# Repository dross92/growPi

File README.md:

# **growPi**

#### Envirologger / Fan Controller for Raspberry Pi ####
This is a 'HAT' for Raspberry Pi 3 B.  The objective of this circuit board is to control and optimize an environment for growing plants.  Integrated Fan controller regulates temperature.

### Connections ###
* Headers for up to five i2c connections (Vcc = 5V)
* Three 4-wire 12v PWM fans
* Three relays (Lights, Fan, Water Pump)
* 12v plug powers entire board & Pi
* Push Button for manual pump control

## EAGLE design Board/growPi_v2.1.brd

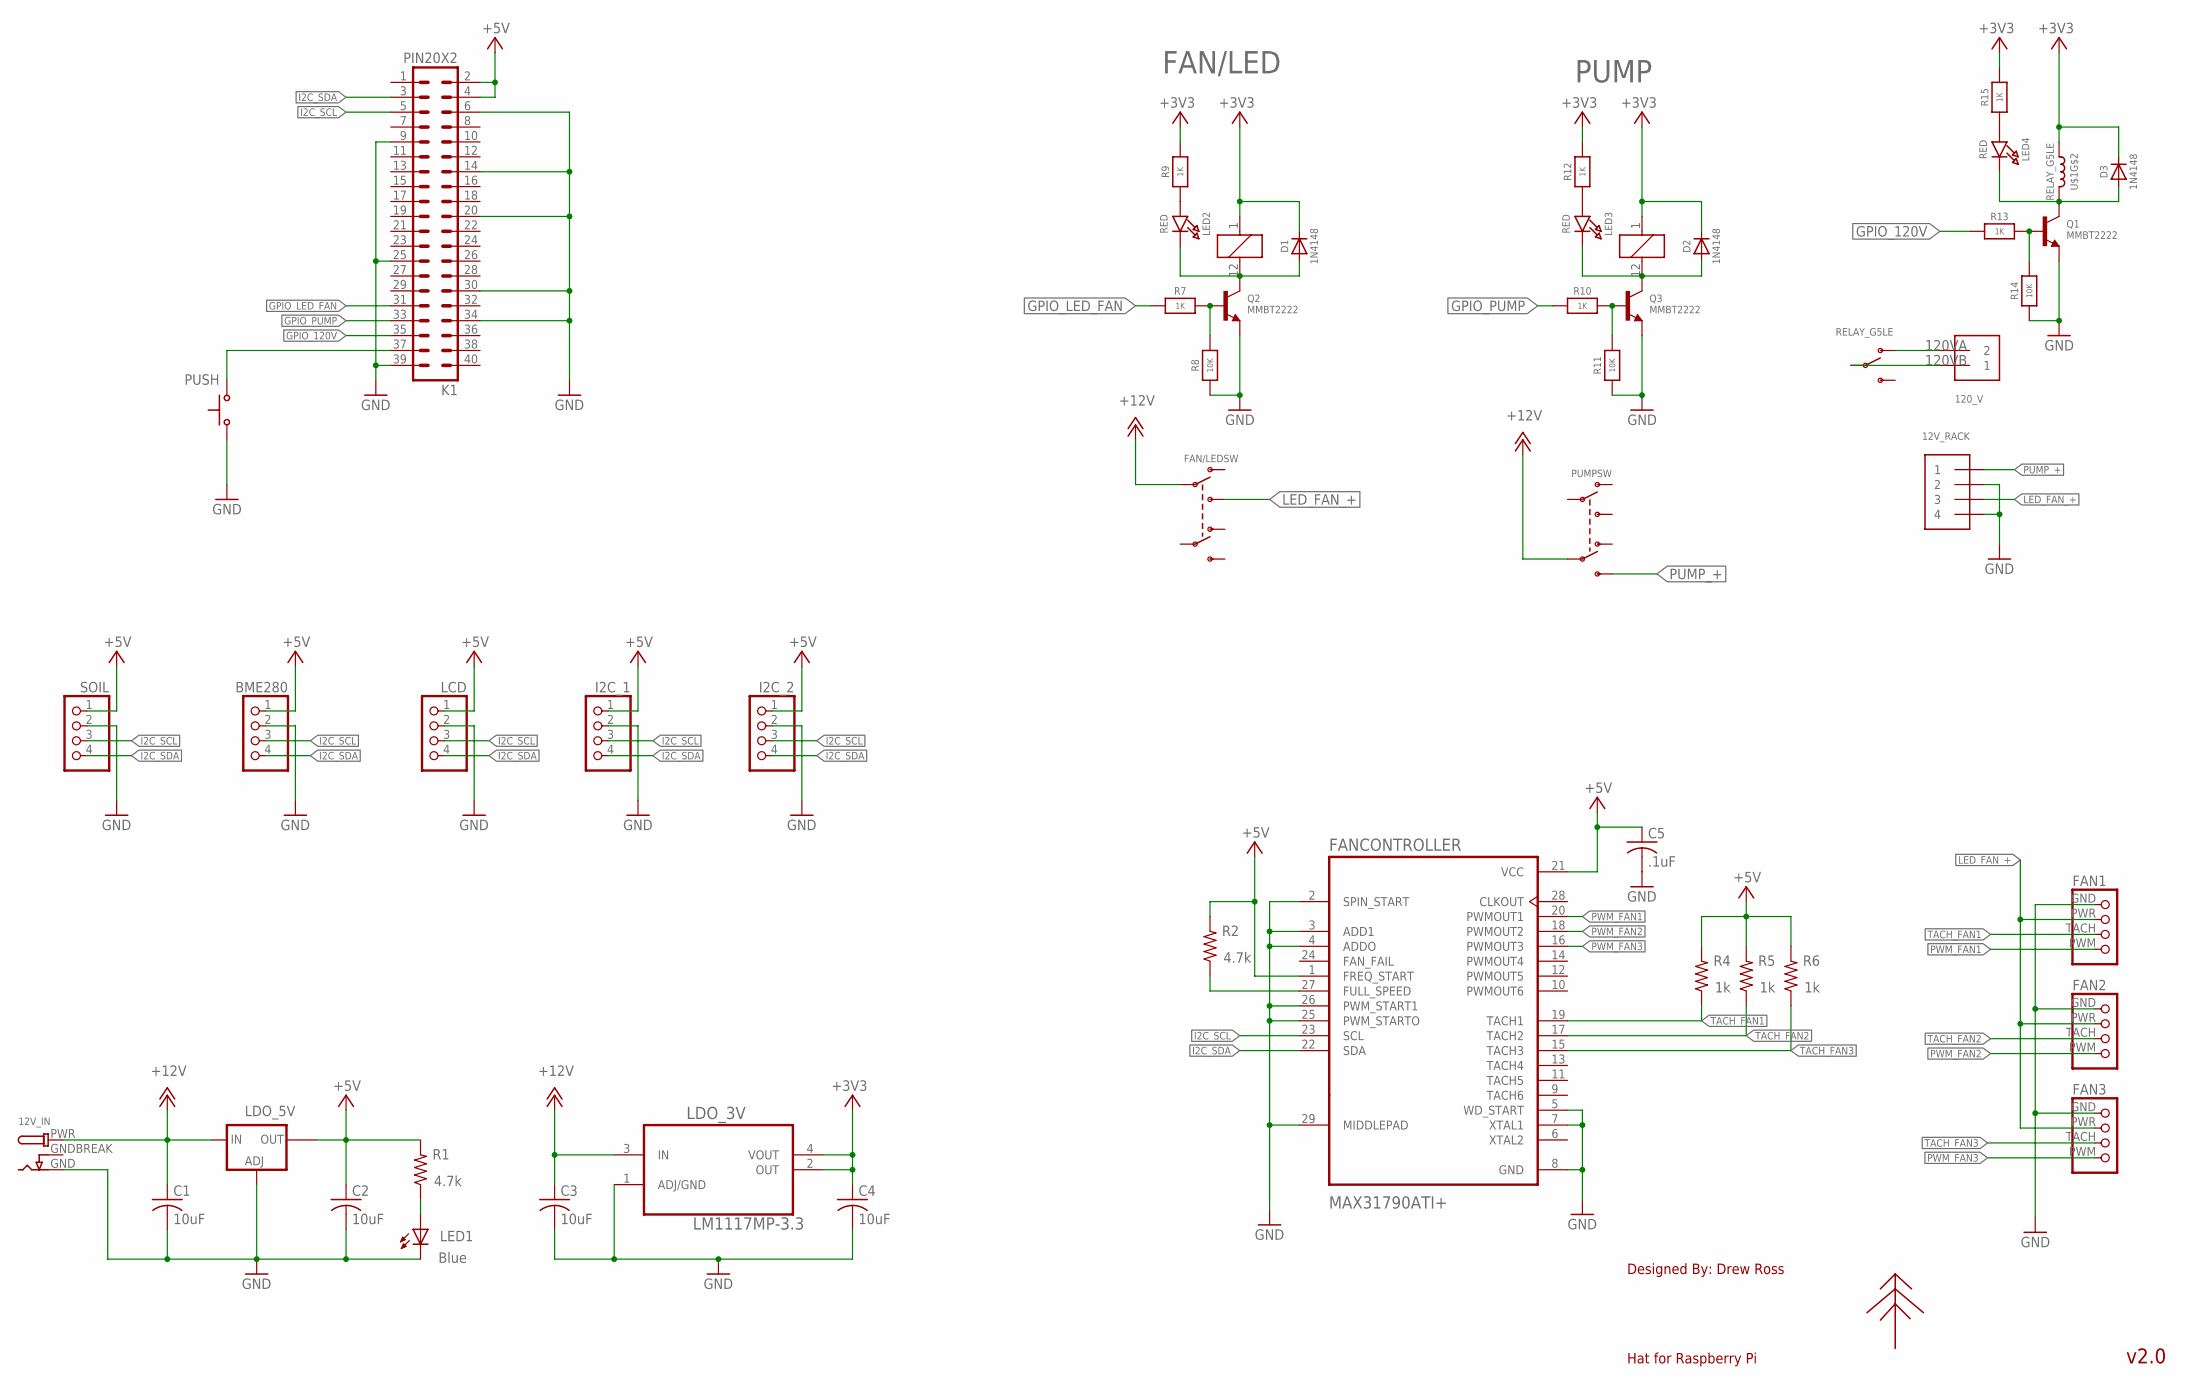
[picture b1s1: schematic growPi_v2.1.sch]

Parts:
12V_IN: DCBARRELSMT_CORRECT; DCJACK_2MM_SMT
12V_RACK: TERMBLOCK_1X4-5.0MM
120_V: TERMBLOCK_1X2-5.0MM
BME280: PINHD-1X4; 1X04
C1, C2, C3, C4: 10uF; C0603
C5: .1uF; C0603
D1, D2, D3: 1N4148; SOD-323
FAN1, FAN2, FAN3: 4PIN-MOLEX-FAN; 4PIN-FAN-HEADER
FAN/LED: RELAY_NONLATCHING-EE2NUH; RELAY_EE2_NOLATCH
FANCONTROLLER: MAX31790ATI+; QFN40P400X400X80-29N
I2C_1, I2C_2: PINHD-1X4; 1X04
K1: PIN20X2; PIN_20X2
LCD: PINHD-1X4; 1X04
LDO_3V: LM1117MP-3.3; SOT230P696X180-4N
LDO_5V: LM1084IS; TO263
LED1: Blue; CHIPLED_0603
LED2, LED3, LED4: RED; CHIPLED_0603_NOOUTLINE
PLANTLOGO: PLANTLOGO; PLANT
PUMP: RELAY_NONLATCHING-EE2NUH; RELAY_EE2_NOLATCH
PUSH: PTS645SSMTR; PTS645-SMD
Q1, Q2, Q3: MMBT2222; SOT23-R
R1, R2: 4.7k; R0603
R4, R5, R6: 1k; R0603
R7, R9, R10, R12, R13, R15: 1K; 0603-NO
R8, R11, R14: 10K; 0603-NO
SOIL: PINHD-1X4; 1X04
U$1: RELAY_G5LE; RELAY_G5LE-1

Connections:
120VA: 120_V.2, U$1.3 (O)
120VB: 120_V.1, U$1.1
+3V3: C4.1, D1.C, D2.C, D3.C, FAN/LED.1, LDO_3V.2 (OUT), LDO_3V.4 (VOUT), PUMP.1, R9.2, R12.2, R15.2, U$1.2 (1)
+5V: BME280.1, C2.1, C5.1, FANCONTROLLER.1 (FREQ_START), FANCONTROLLER.21 (VCC), I2C_1.1, I2C_2.1, K1.2, K1.4, LCD.1, LDO_5V.2 (OUT), R1.2, R2.2, R4.2, R5.2, R6.2, SOIL.1
+12V: 12V_IN.PWR, C1.1, C3.1, FAN/LED.9 (P1), LDO_3V.3 (IN), LDO_5V.3 (IN), PUMP.4 (P2)
GND: 12V_IN.GND, 12V_RACK.2, 12V_RACK.4, BME280.2, C1.2, C2.2, C3.2, C4.2, C5.2, FAN1.GND (1), FAN2.GND (1), FAN3.GND (1), FANCONTROLLER.2 (SPIN_START), FANCONTROLLER.3 (ADD1), FANCONTROLLER.4 (ADDO), FANCONTROLLER.5 (WD_START), FANCONTROLLER.7 (XTAL1), FANCONTROLLER.8 (GND), FANCONTROLLER.25 (PWM_STARTO), FANCONTROLLER.26 (PWM_START1), FANCONTROLLER.29 (MIDDLEPAD), I2C_1.2, I2C_2.2, K1.6, K1.9, K1.14, K1.20, K1.25, K1.30, K1.34, K1.39, LCD.2, LDO_3V.1 (ADJ/GND), LDO_5V.1 (ADJ), LED1.C, PUSH.1, PUSH.2, Q1.2 (E), Q2.2 (E), Q3.2 (E), R8.1, R11.1, R14.1, SOIL.2
GNDBREAK: 12V_IN.GNDBREAK
GPIO_120V: K1.35, R13.1
GPIO_LED_FAN: K1.31, R7.1
GPIO_PUMP: K1.33, R10.1
I2C_SCL: BME280.3, FANCONTROLLER.23 (SCL), I2C_1.3, I2C_2.3, K1.5, LCD.3, SOIL.3
I2C_SDA: BME280.4, FANCONTROLLER.22 (SDA), I2C_1.4, I2C_2.4, K1.3, LCD.4, SOIL.4
LED_FAN_+: 12V_RACK.3, FAN1.PWR (2), FAN2.PWR (2), FAN3.PWR (2), FAN/LED.8 (S1)
unnamed: FANCONTROLLER.27 (FULL_SPEED), R2.1
unnamed: D1.A, FAN/LED.12 (2), LED2.C, Q2.3 (C)
unnamed: Q2.1 (B), R7.2, R8.2
unnamed: LED2.A, R9.1
unnamed: D2.A, LED3.C, PUMP.12 (2), Q3.3 (C)
unnamed: Q3.1 (B), R10.2, R11.2
unnamed: D3.A, LED4.C, Q1.3 (C), U$1.5 (2)
unnamed: LED3.A, R12.1
unnamed: LED1.A, R1.1
unnamed: K1.37, PUSH.3 (S), PUSH.4 (S)
unnamed: Q1.1 (B), R13.2, R14.2
unnamed: LED4.A, R15.1
PUMP_+: 12V_RACK.1, PUMP.5 (S2)
PWM_FAN1: FAN1.PWM (4), FANCONTROLLER.20 (PWMOUT1)
PWM_FAN2: FAN2.PWM (4), FANCONTROLLER.18 (PWMOUT2)
PWM_FAN3: FAN3.PWM (4), FANCONTROLLER.16 (PWMOUT3)
TACH_FAN1: FAN1.TACH (3), FANCONTROLLER.19 (TACH1), R4.1
TACH_FAN2: FAN2.TACH (3), FANCONTROLLER.17 (TACH2), R5.1
TACH_FAN3: FAN3.TACH (3), FANCONTROLLER.15 (TACH3), R6.1

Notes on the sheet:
Designed By:
Hat for Raspberry Pi
Drew Ross
v2.0

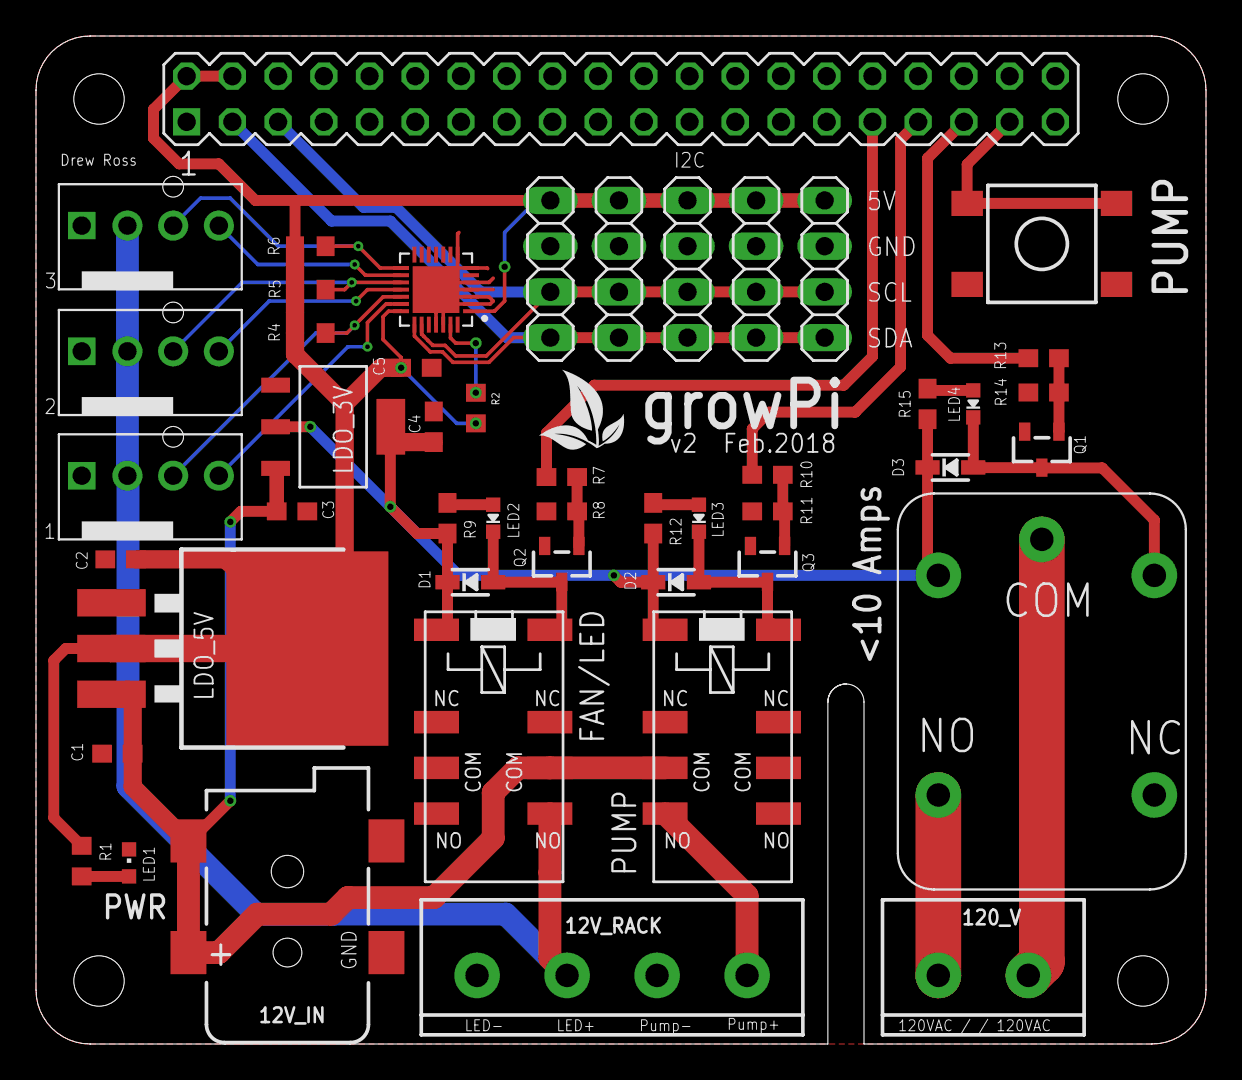
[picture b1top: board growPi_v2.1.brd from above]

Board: 2 copper layers, 65.0 x 56.0 mm, 49 parts (0 on the bottom side), 31 nets.

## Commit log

2018-02-12 updated render

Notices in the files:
parts and their libraries:
microbuilder: This work is placed in the public domain, and may be freely used for commercial and non-commercial work with the following conditions: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
switch-ck: Copyright (C) 2011, Bob Starr
